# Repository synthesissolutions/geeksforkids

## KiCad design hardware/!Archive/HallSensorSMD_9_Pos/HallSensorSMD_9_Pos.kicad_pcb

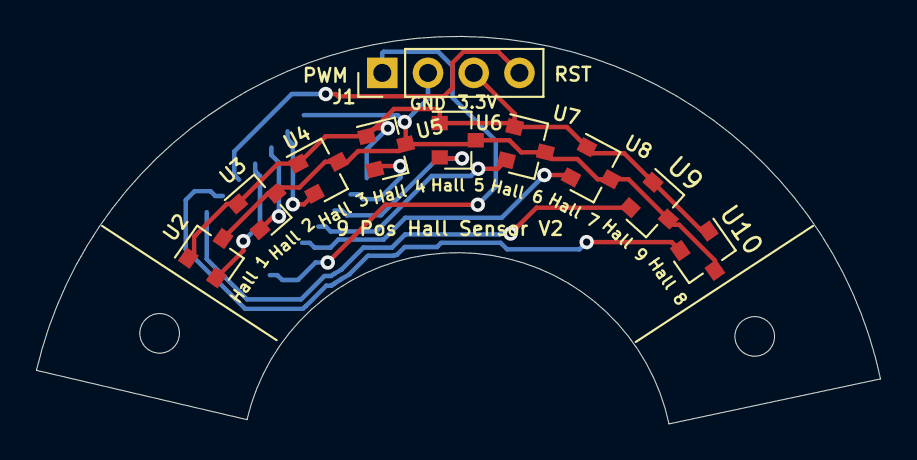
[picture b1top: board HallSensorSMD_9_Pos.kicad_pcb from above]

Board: 2 copper layers, 46.9 x 21.5 mm, 11 parts (1 on the bottom side), 13 nets.

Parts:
J1: Power/Signal; PinHeader_1x04_P2.54mm_Vertical
U1: ATtiny814-SS; SOIC-14_3.9x8.7mm_P1.27mm
U2: Hall 1; SOT-23
U3: Hall 2; SOT-23
U4: Hall 3; SOT-23
U5: Hall 4; SOT-23
U6: Hall 5; SOT-23
U7: Hall 6; SOT-23
U8: Hall 7; SOT-23
U9: Hall 9; SOT-23
U10: Hall 8; SOT-23

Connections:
+3V3: J1.3, U1.1, U2.1, U3.1, U4.1, U5.1, U6.1, U7.1, U8.1, U9.1, U10.1
GND: J1.2, U1.14, U2.3, U3.3, U4.3, U5.3, U6.3, U7.3, U8.3, U9.3, U10.3
unnamed: J1.1, U1.7
unnamed: J1.4, U1.10
unnamed: U1.2, U5.2
unnamed: U1.3, U6.2
unnamed: U1.4, U7.2
unnamed: U1.5, U8.2
unnamed: U1.8, U9.2
unnamed: U1.9, U10.2
unnamed: U1.11, U2.2
unnamed: U1.12, U3.2
unnamed: U1.13, U4.2

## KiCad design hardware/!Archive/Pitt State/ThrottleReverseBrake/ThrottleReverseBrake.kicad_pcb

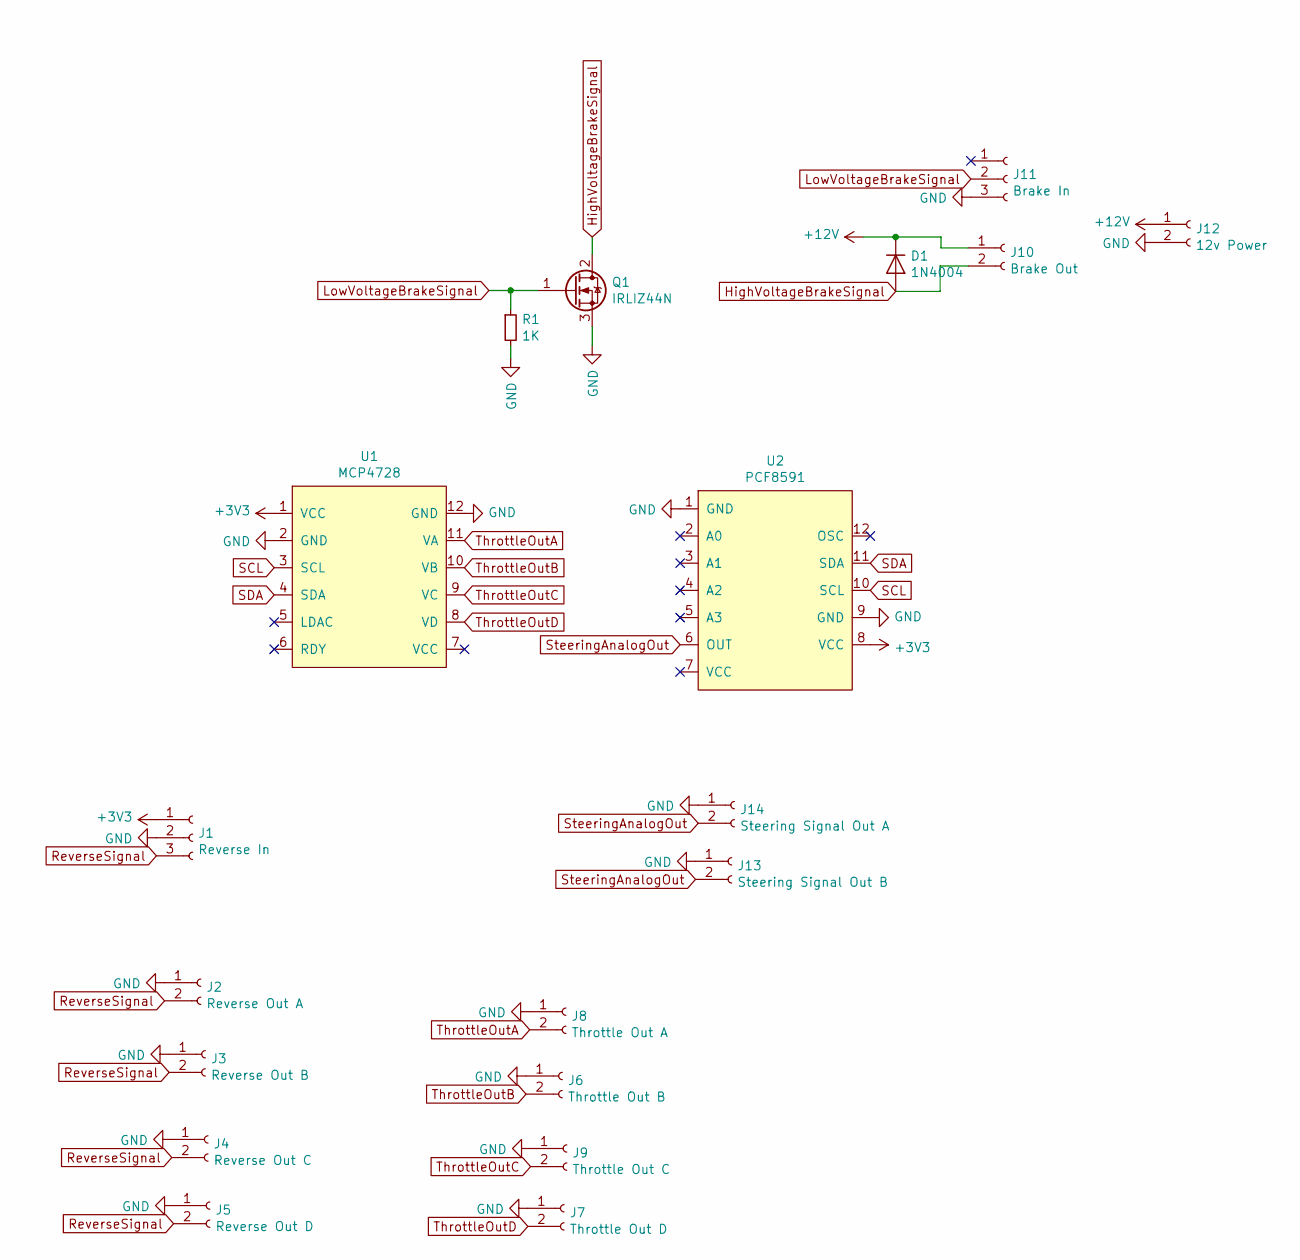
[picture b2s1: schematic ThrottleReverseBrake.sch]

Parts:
D1: 1N4004; D_DO-41_SOD81_P10.16mm_Horizontal
J1: Reverse In; JST_XH_B3B-XH-A_1x03_P2.54mm_Vertical
J2: Reverse Out A; JST_XH_B2B-XH-A_1x02_P2.54mm_Vertical
J3: Reverse Out B; JST_XH_B2B-XH-A_1x02_P2.54mm_Vertical
J4: Reverse Out C; JST_XH_B2B-XH-A_1x02_P2.54mm_Vertical
J5: Reverse Out D; JST_XH_B2B-XH-A_1x02_P2.54mm_Vertical
J6: Throttle Out B; JST_XH_B2B-XH-A_1x02_P2.54mm_Vertical
J7: Throttle Out D; JST_XH_B2B-XH-A_1x02_P2.54mm_Vertical
J8: Throttle Out A; JST_XH_B2B-XH-A_1x02_P2.54mm_Vertical
J9: Throttle Out C; JST_XH_B2B-XH-A_1x02_P2.54mm_Vertical
J10: Brake Out; TerminalBlock_bornier-2_P5.08mm
J11: Brake In; JST_XH_B3B-XH-A_1x03_P2.54mm_Vertical
J12: 12v Power; TerminalBlock_bornier-2_P5.08mm
J13: Steering Signal Out B; JST_XH_B2B-XH-A_1x02_P2.54mm_Vertical
J14: Steering Signal Out A; JST_XH_B2B-XH-A_1x02_P2.54mm_Vertical
Q1: IRLIZ44N; TO-220F-3_Vertical
R1: 1K; R_0805_2012Metric_Pad1.15x1.40mm_HandSolder
U1: MCP4728; Adafruit_MCP4728
U2: PCF8591; Adafruit_PCF8591

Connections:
+3V3: J1.1, U1.1 (VCC), U2.8 (VCC)
+12V: D1.1 (K), J10.1, J12.1
GND: J1.2, J2.1, J3.1, J4.1, J5.1, J6.1, J7.1, J8.1, J9.1, J11.3, J12.2, J13.1, J14.1, Q1.3 (S), R1.2, U1.2 (GND), U1.12 (GND), U2.1 (GND), U2.9 (GND)
HighVoltageBrakeSignal: D1.2 (A), J10.2, Q1.2 (D)
LowVoltageBrakeSignal: J11.2, Q1.1 (G), R1.1
ReverseSignal: J1.3, J2.2, J3.2, J4.2, J5.2
SCL: U1.3 (SCL), U2.10 (SCL)
SDA: U1.4 (SDA), U2.11 (SDA)
SteeringAnalogOut: J13.2, J14.2, U2.6 (OUT)
ThrottleOutA: J8.2, U1.11 (VA)
ThrottleOutB: J6.2, U1.10 (VB)
ThrottleOutC: J9.2, U1.9 (VC)
ThrottleOutD: J7.2, U1.8 (VD)

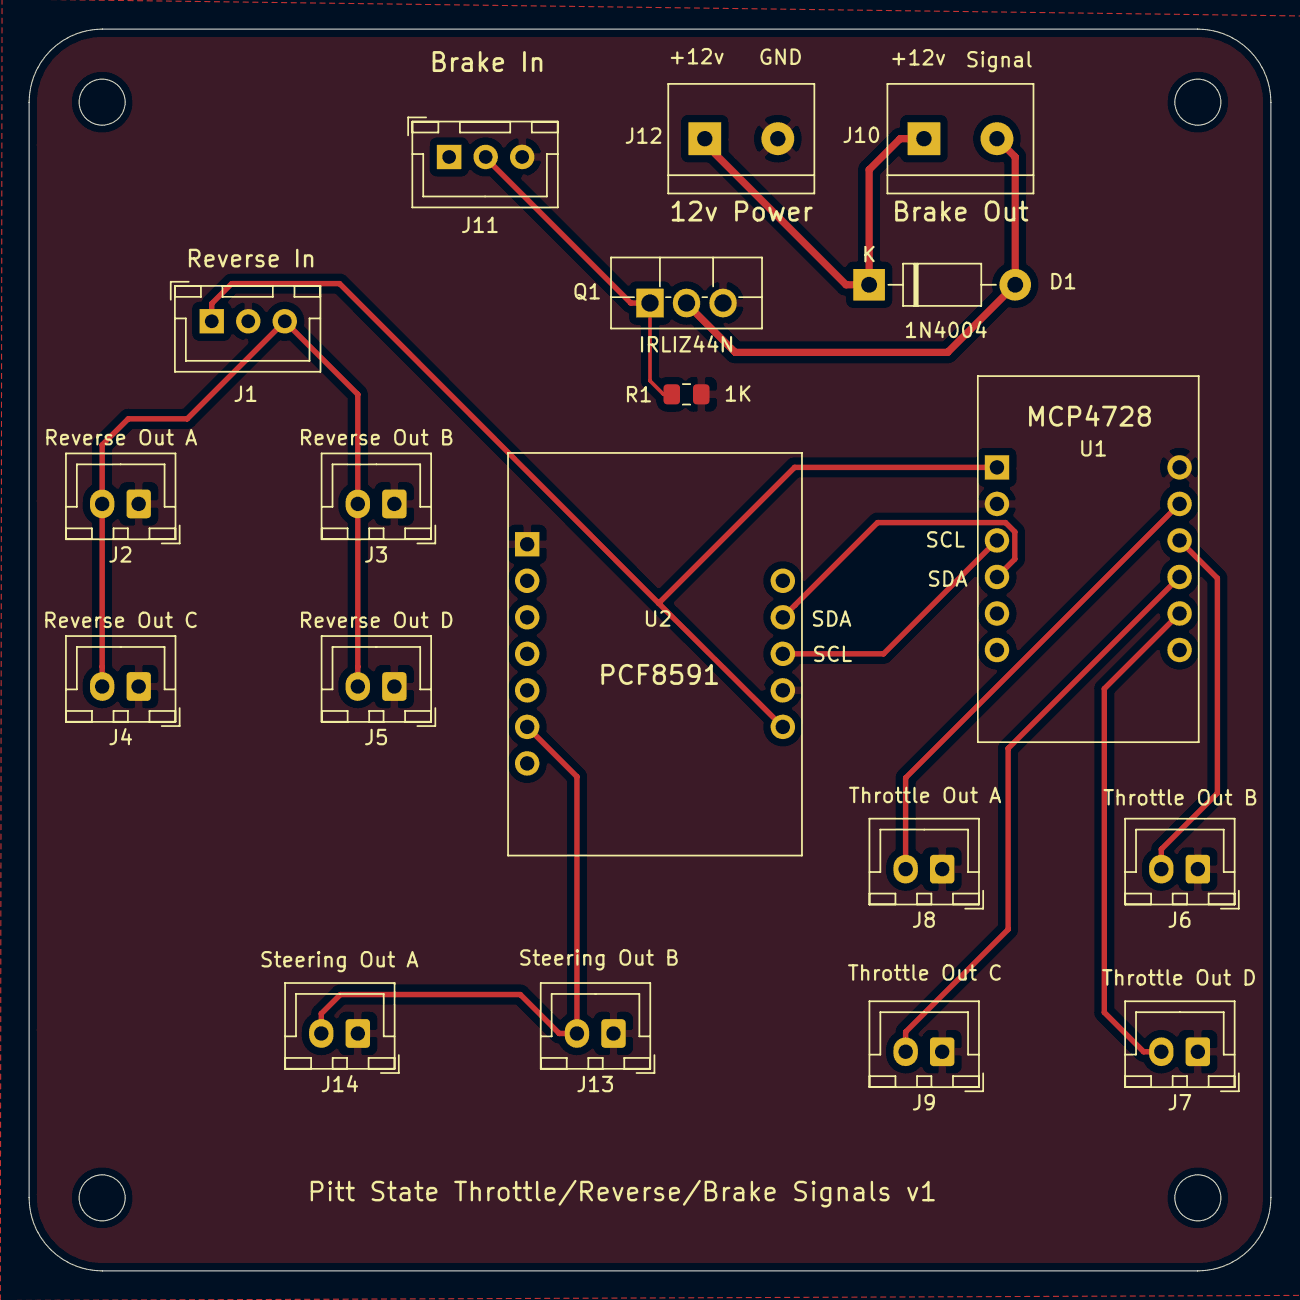
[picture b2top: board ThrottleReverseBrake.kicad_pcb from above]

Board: 2 copper layers, 86.4 x 86.4 mm, 19 parts (0 on the bottom side), 13 nets.

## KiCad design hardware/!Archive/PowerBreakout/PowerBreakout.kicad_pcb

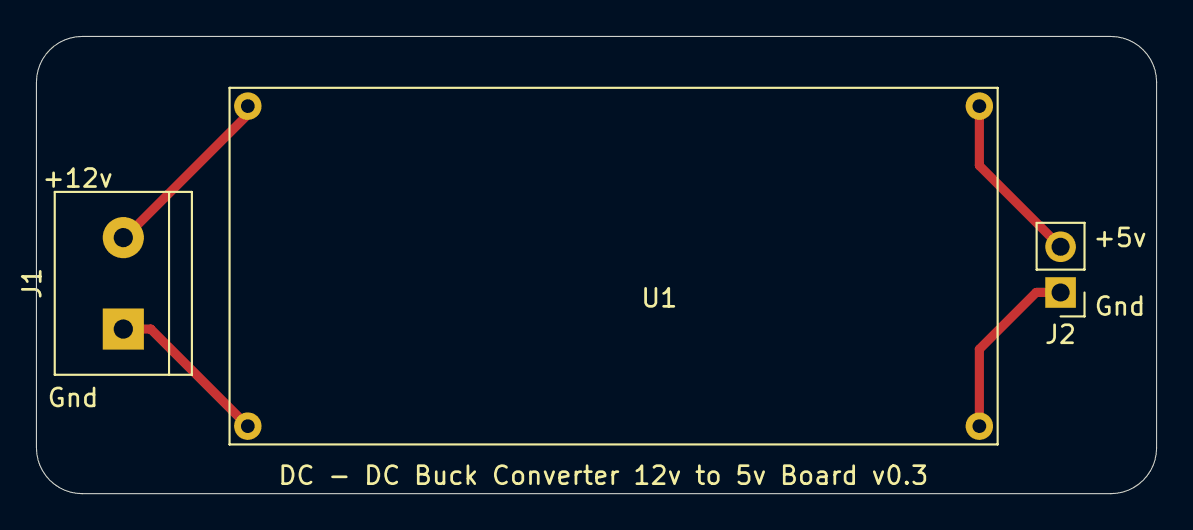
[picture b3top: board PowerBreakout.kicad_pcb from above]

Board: 2 copper layers, 62.2 x 25.4 mm, 3 parts (0 on the bottom side), 4 nets.

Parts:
J1: Screw_Terminal_01x02; TerminalBlock_bornier-2_P5.08mm
J2: Conn_01x02_Male; PinHeader_1x02_P2.54mm_Vertical
U1: LM2596Adj

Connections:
unnamed: J1.1, U1.2
unnamed: J1.2, U1.1
unnamed: J2.1, U1.4
unnamed: J2.2, U1.3

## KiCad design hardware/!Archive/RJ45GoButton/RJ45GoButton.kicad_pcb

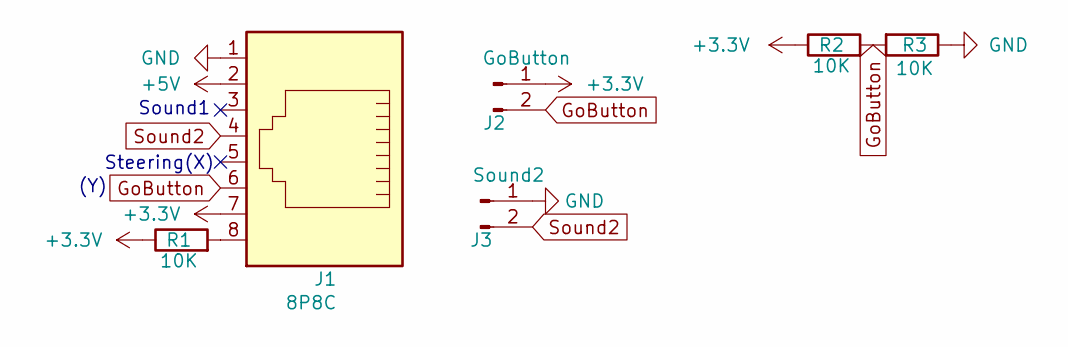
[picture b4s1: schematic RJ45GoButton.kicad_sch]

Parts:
J1: 8P8C; RJ45_x08_Tab_Up
J2: GoButton; JST_XH_B2B-XH-A_1x02_P2.50mm_Vertical
J3: Sound2; JST_XH_B2B-XH-A_1x02_P2.50mm_Vertical
R1, R2, R3: 10K; R_0805_2012Metric_Pad1.20x1.40mm_HandSolder; MPN C17444

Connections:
+3.3V: J1.7, J2.1, R1.1, R2.1
+5V: J1.2
GND: J1.1, J3.1, R3.1
GoButton: J1.6, J2.2, R2.2, R3.2
unnamed: J1.8, R1.2
Sound2: J1.4, J3.2

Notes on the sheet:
Sound1
Steering(X)
(Y)

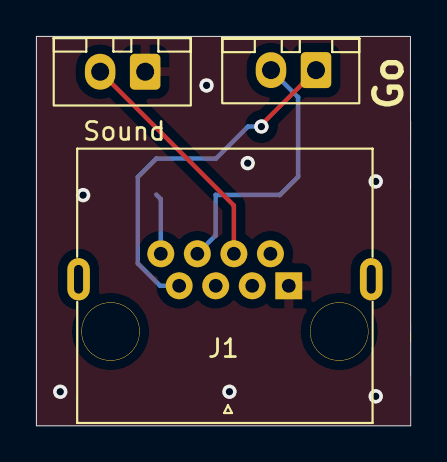
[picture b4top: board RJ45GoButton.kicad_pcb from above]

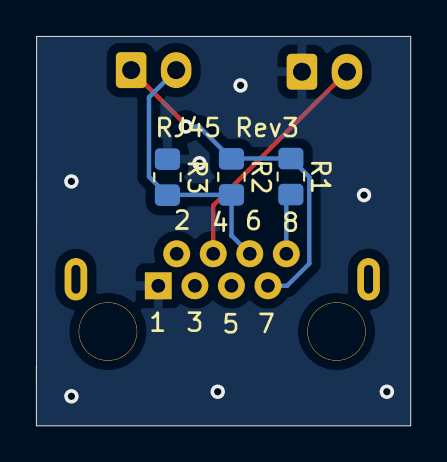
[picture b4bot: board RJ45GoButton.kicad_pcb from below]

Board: 2 copper layers, 20.8 x 21.6 mm, 6 parts (3 on the bottom side), 5 nets.

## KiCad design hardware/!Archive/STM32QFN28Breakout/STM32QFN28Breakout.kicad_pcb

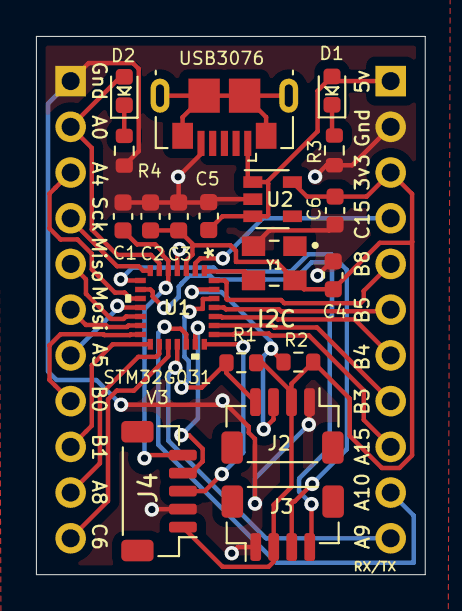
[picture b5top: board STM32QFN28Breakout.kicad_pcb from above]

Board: 2 copper layers, 21.6 x 29.9 mm, 21 parts (0 on the bottom side), 31 nets.

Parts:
C1, C2, C4: 100nF; C_0603_1608Metric
C3: 10uF; C_0603_1608Metric
C5, C6: 1uF; C_0603_1608Metric
D1: Power LED; LED_0603_1608Metric
D2: User LED; LED_0603_1608Metric
J1: USB3076; USB_Micro-B_GCT_USB3076-30-A
J2, J3: Conn_01x04_Male; JST_SH_BM04B-SRSS-TB_1x04-1MP_P1.00mm_Vertical
J4: Conn_01x05_Male; JST_SH_BM05B-SRSS-TB_1x05-1MP_P1.00mm_Vertical
J5, J6: Conn_01x11_Male; PinHeader_1x11_P2.54mm_Vertical
R1, R2: 10K; R_0603_1608Metric
R3: 1K; R_0603_1608Metric
R4: 470; R_0603_1608Metric
U1: STM32G031F4Px; STM32G031G8U6
U2: AP2112K-3.3; SOT-23-5
Y1: ECS-3225MVQ-160-BP-TR; OSC_ECS-3225MVQ-160-BP-TR

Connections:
+3V3: C2.1, C3.1, C4.2, C6.2, J2.2, J3.2, J4.1, J6.3, R1.2, R2.2, U1.3 (VDD), U2.5 (VOUT), Y1.4 (VDD)
+5V: C5.1, D1.2 (A), J1.1 (VBUS), J6.1, U2.1 (VIN), U2.3 (EN)
/RESET: C1.1, J4.5, U1.5 (PF2-NRST)
GND: C1.2, C2.2, C3.2, C4.1, C5.2, C6.1, J1.5 (GND), J2.1, J3.1, J4.2, J5.1, J6.2, R3.1, R4.2, U1.4 (VSS), U2.2 (GND), Y1.2 (GND)
MISO: J5.5, U1.12 (PA6)
MOSI: J5.6, U1.13 (PA7)
unnamed: D1.1 (K), R3.2
unnamed: D2.1 (K), R4.1
OscillatorIn: U1.1 (PC14-OSC32_IN), Y1.3 (OUTPUT)
PA0: D2.2 (A), J5.2, U1.6 (PA0)
PA4: J5.3, U1.10 (PA4)
PA5: J5.7, U1.11 (PA5)
PA8: J5.10, U1.16 (PA8)
PA9: J6.11, U1.18 (PA11PA9)
PA10: J6.10, U1.19 (PA12PA10)
PA15: J6.9, U1.22 (PA15)
PB0: J5.8, U1.14 (PB0)
PB1: J5.9, U1.15 (PB1)
PB3: J6.8, U1.23 (PB3)
PB4: J6.7, U1.24 (PB4)
PB5: J6.6, U1.25 (PB5)
PB8: J6.5, U1.28 (PB8)
PC6: J5.11, U1.17 (PC6)
PC15: J6.4, U1.2 (PC15-OSC32_OUT)
RX: J3.4, U1.9 (PA3)
SCK: J5.4, U1.7 (PA1)
SCL: J2.4, R1.1, U1.26 (PB6)
SDA: J2.3, R2.1, U1.27 (PB7)
SWCLK: J4.3, U1.21 (PA14-BOOT0)
SWDIO: J4.4, U1.20 (PA13)
TX: J3.3, U1.8 (PA2)

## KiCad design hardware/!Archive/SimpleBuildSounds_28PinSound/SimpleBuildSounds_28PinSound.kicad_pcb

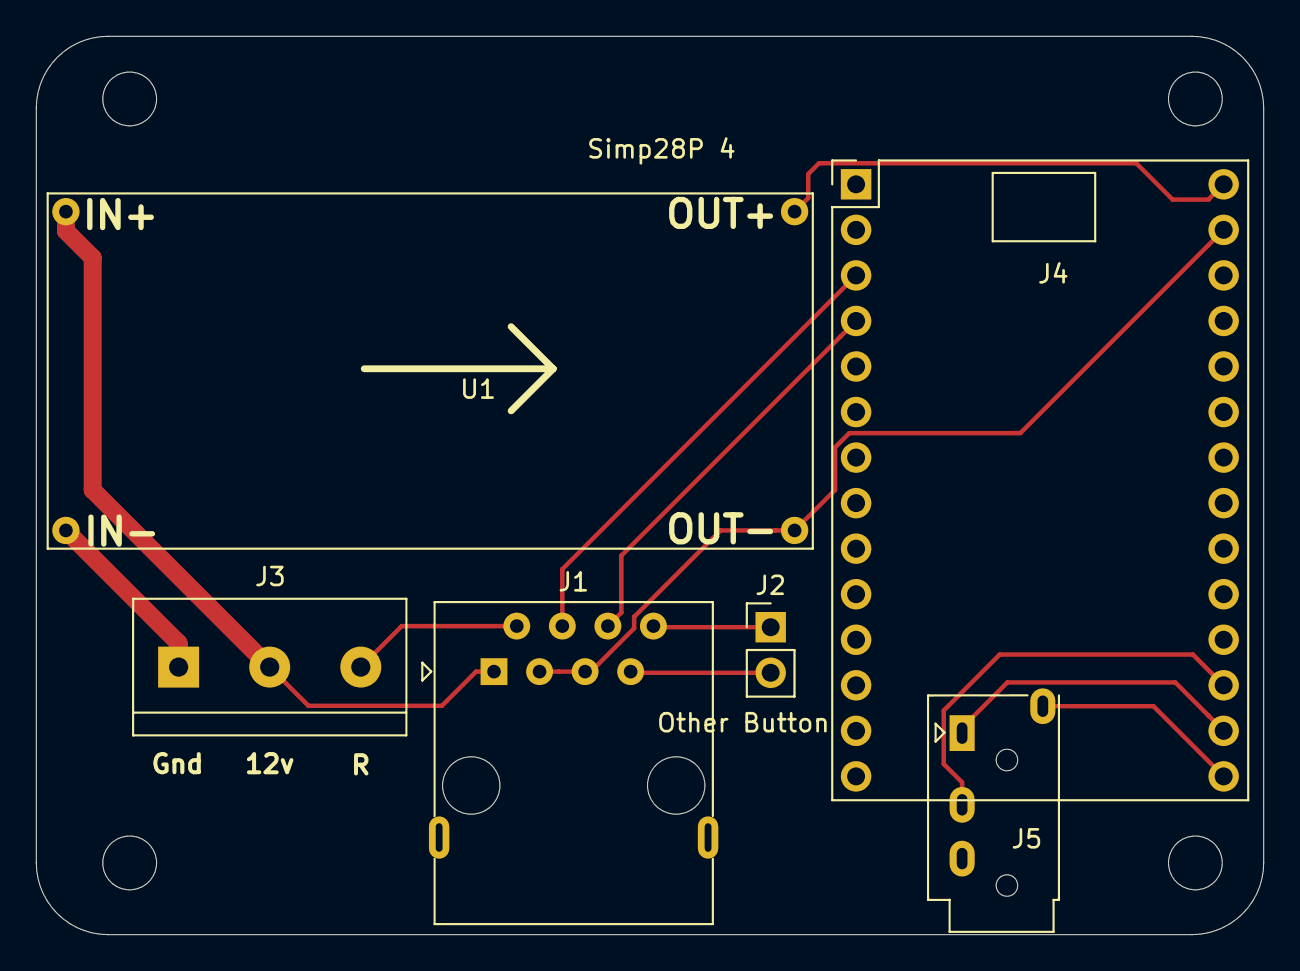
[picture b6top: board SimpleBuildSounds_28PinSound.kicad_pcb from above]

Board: 2 copper layers, 68.5 x 50.1 mm, 10 parts (0 on the bottom side), 12 nets.

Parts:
J1: RJ45; RJ45_x08_Horizontal_tabs
J2: Other Button; PinHeader_1x02_P2.54mm_Vertical
J3: Power and GoBtn; TerminalBlock_bornier-2_P5.08mm
J4: FX_Sound; FXSound_HeadPhone_2x14_P2.54mm_Short
J5: AudioJack4; Jack_3.5mm_PJ320A_Horizontal
REF: MountingHole_3mm
REF#2, REF#3, REF#4: MountingHole_3mm
U1: LM2596; Regulator_LM2596Adj

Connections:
+5V: J4.2, U1.4
+12V: J1.1, J3.2, U1.2
GND: J1.3, J1.5, J4.4, U1.6
GNDPWR: J3.1, U1.1
unnamed: J1.2, J3.3
unnamed: J1.4, J4.5
unnamed: J1.6, J4.7
unnamed: J1.7, J2.2
unnamed: J1.8, J2.1
unnamed: J4.24, J5.R1
unnamed: J4.26, J5.T
unnamed: J4.28, J5.S

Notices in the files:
parts and their libraries:
Copyright 2021 Accelerated Designs. All rights reserved.
